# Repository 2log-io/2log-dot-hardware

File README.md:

# 2log-dot-hardware

This repository contains the KiCad Project for the 2log Dot. The hardware is designed to be used with [2log Dot](https://github.com/2log-io/2log-dot "2log Dot Firmware")

## Parts

The PCB consists of a 4-Layer stack. All required parts are through hole components with the exception of the capacitor C1 which is a combined footprint.
Besides the PCB itself you need the following parts:
  * 24 Led WS2812B Ring with 4 contacts (diameter 66mm)
  * SMD Capacitor 5mm diameter, about 10uF
  * (alternative) THT Capacitor, about 10uF
  * Wemos D1 mini ESP32 (ESP8266 will not work)
  * PN532 RFID Reader V3 (red modules, sold under elechouse brand or clones)
  * mini pushbutton (the tiny black/silver ones)
  * _(optional) 14 Pin Male and 13 Pin Female 2.54mm Pin Header/Socket for expansion port_
  
## Images

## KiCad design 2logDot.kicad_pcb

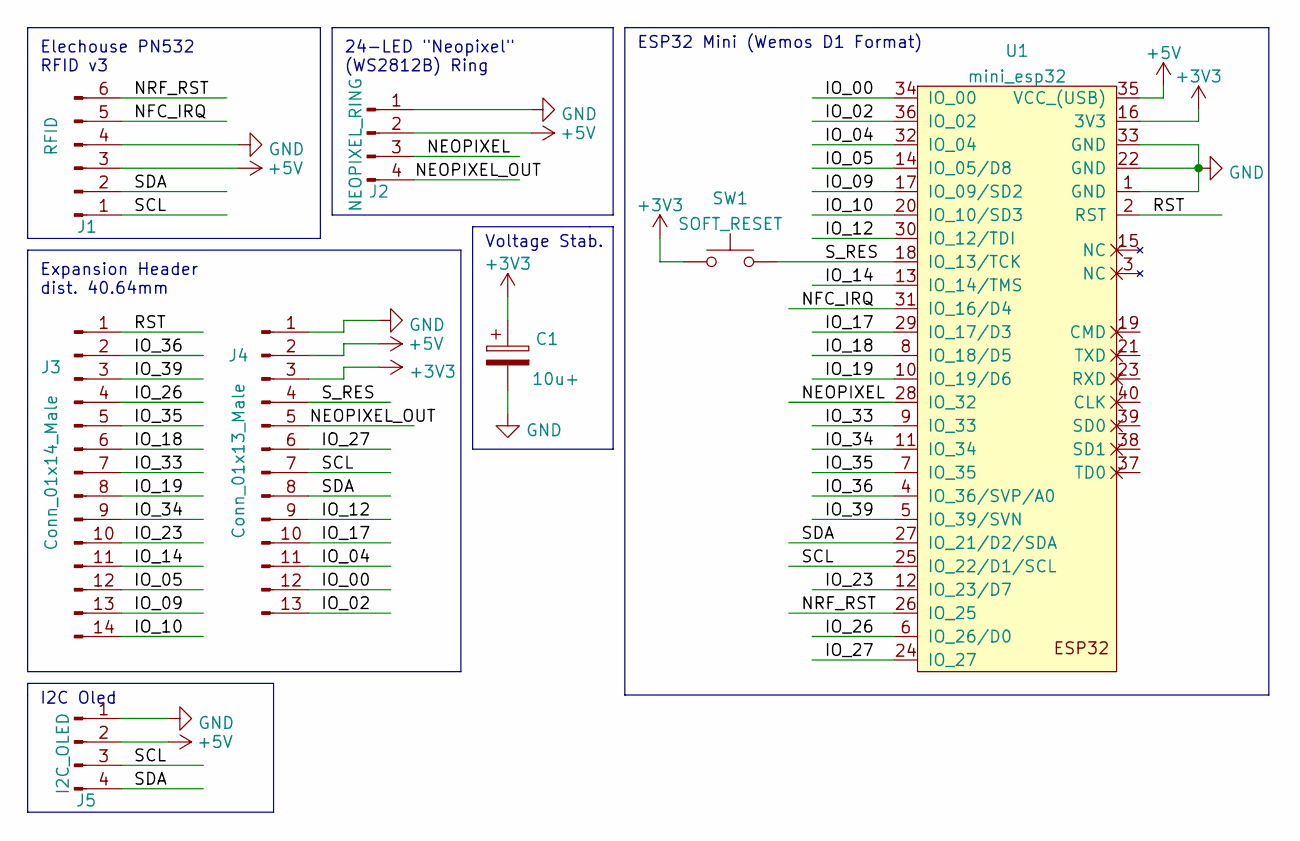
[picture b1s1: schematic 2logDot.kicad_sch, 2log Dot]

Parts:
C1: 10u+; CP_Elec_5x3
J1: RFID; 2log_elechouse_pn532
J2: NEOPIXEL_RING; PinHeader_1x04_P2.54mm_Vertical
J3: Conn_01x14_Male; PinHeader_1x14_P2.54mm_Vertical
J4: Conn_01x13_Male; PinSocket_1x13_P2.54mm_Vertical
J5: I2C_OLED; PinHeader_1x04_P2.54mm_Vertical
SW1: SOFT_RESET; SW_PUSH_6mm
U1: mini_esp32; ESP32_mini

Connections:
+3V3: C1.1, J4.3, SW1.1, U1.16 (3V3); also elsewhere on the board
+5V: J1.3, J2.2, J4.2, J5.2, U1.35 (VCC_(USB))
/IO_00: J4.12, U1.34 (IO_00)
/IO_02: J4.13, U1.36 (IO_02)
/IO_04: J4.11, U1.32 (IO_04)
/IO_05: J3.12, U1.14 (IO_05/D8)
/IO_09: J3.13, U1.17 (IO_09/SD2)
/IO_10: J3.14, U1.20 (IO_10/SD3)
/IO_12: J4.9, U1.30 (IO_12/TDI)
/IO_14: J3.11, U1.13 (IO_14/TMS)
/IO_17: J4.10, U1.29 (IO_17/D3)
/IO_18: J3.6, U1.8 (IO_18/D5)
/IO_19: J3.8, U1.10 (IO_19/D6)
/IO_23: J3.10, U1.12 (IO_23/D7)
/IO_26: J3.4, U1.6 (IO_26/D0)
/IO_27: J4.6, U1.24 (IO_27)
/IO_33: J3.7, U1.9 (IO_33)
/IO_34: J3.9, U1.11 (IO_34)
/IO_35: J3.5, U1.7 (IO_35)
/IO_36: J3.2, U1.4 (IO_36/SVP/A0)
/IO_39: J3.3, U1.5 (IO_39/SVN)
/NEOPIXEL: J2.3, U1.28 (IO_32)
/NEOPIXEL_OUT: J2.4, J4.5
/NFC_IRQ: J1.5, U1.31 (IO_16/D4)
/NRF_RST: J1.6, U1.26 (IO_25)
/RST: J3.1, U1.2 (RST)
/SCL: J1.1, J4.7, J5.3, U1.25 (IO_22/D1/SCL)
/SDA: J1.2, J4.8, J5.4, U1.27 (IO_21/D2/SDA)
/S_RES: J4.4, SW1.2, U1.18 (IO_13/TCK)
GND: C1.2, J1.4, J2.1, J4.1, J5.1, U1.1 (GND), U1.22 (GND), U1.33 (GND); also elsewhere on the board

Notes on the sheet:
I2C Oled
ESP32 Mini (Wemos D1 Format)
24-LED "Neopixel" (WS2812B) Ring
Voltage Stab.
Elechouse PN532 RFID v3
Expansion Header dist. 40.64mm

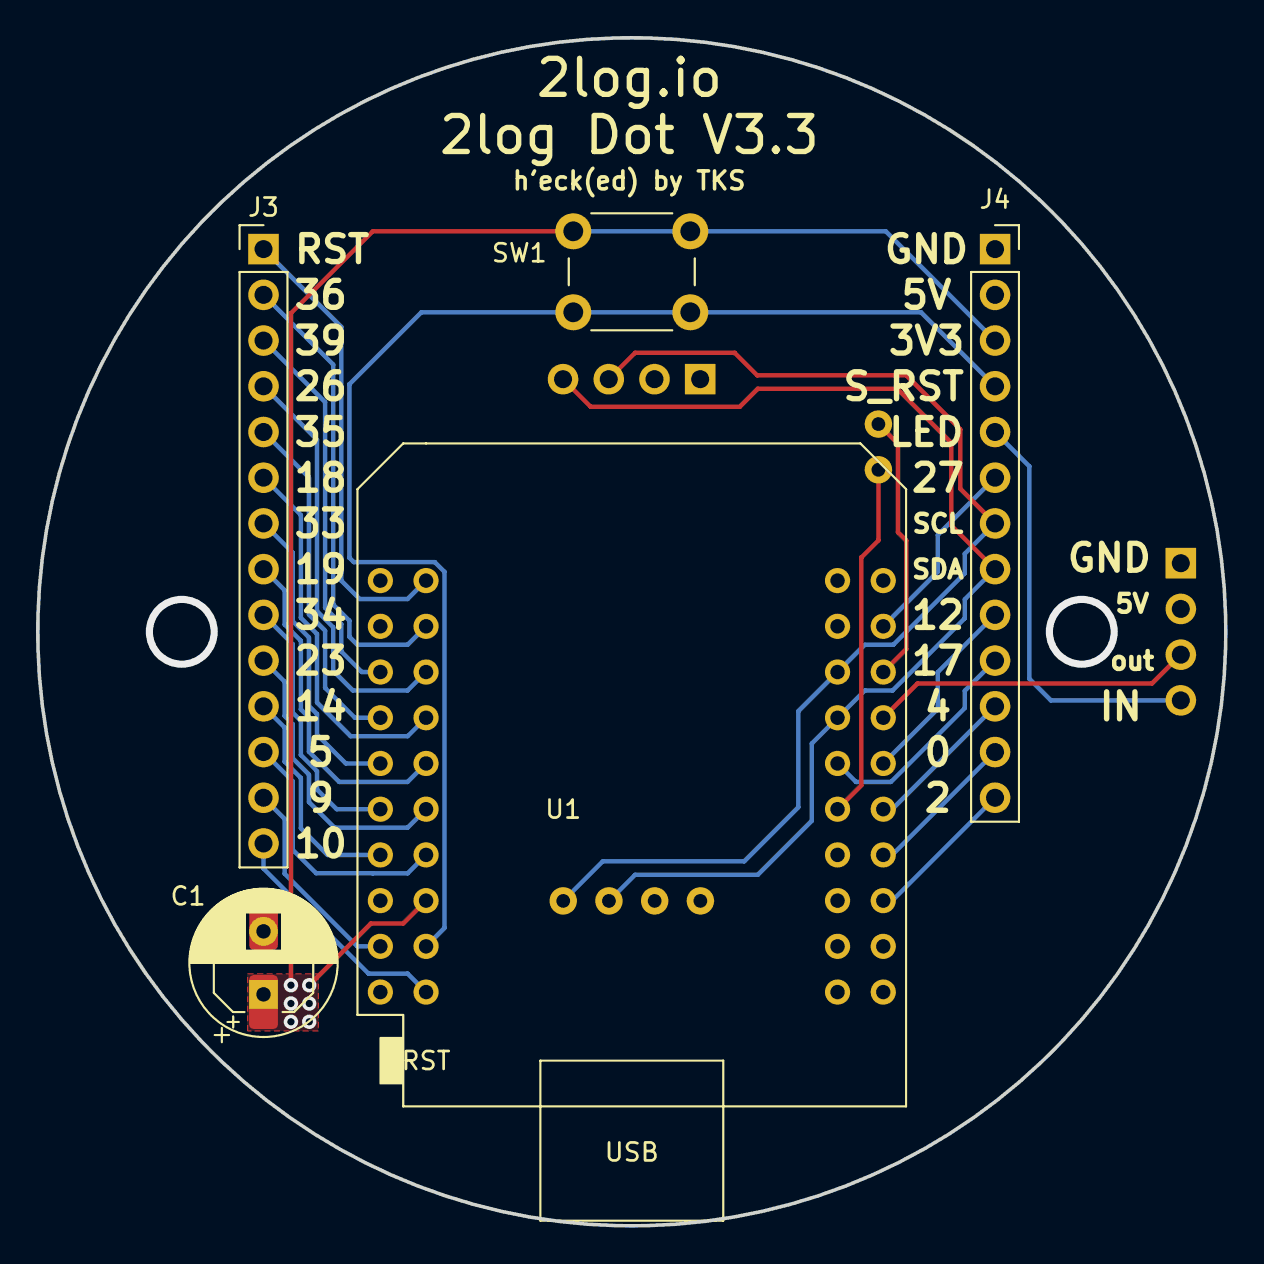
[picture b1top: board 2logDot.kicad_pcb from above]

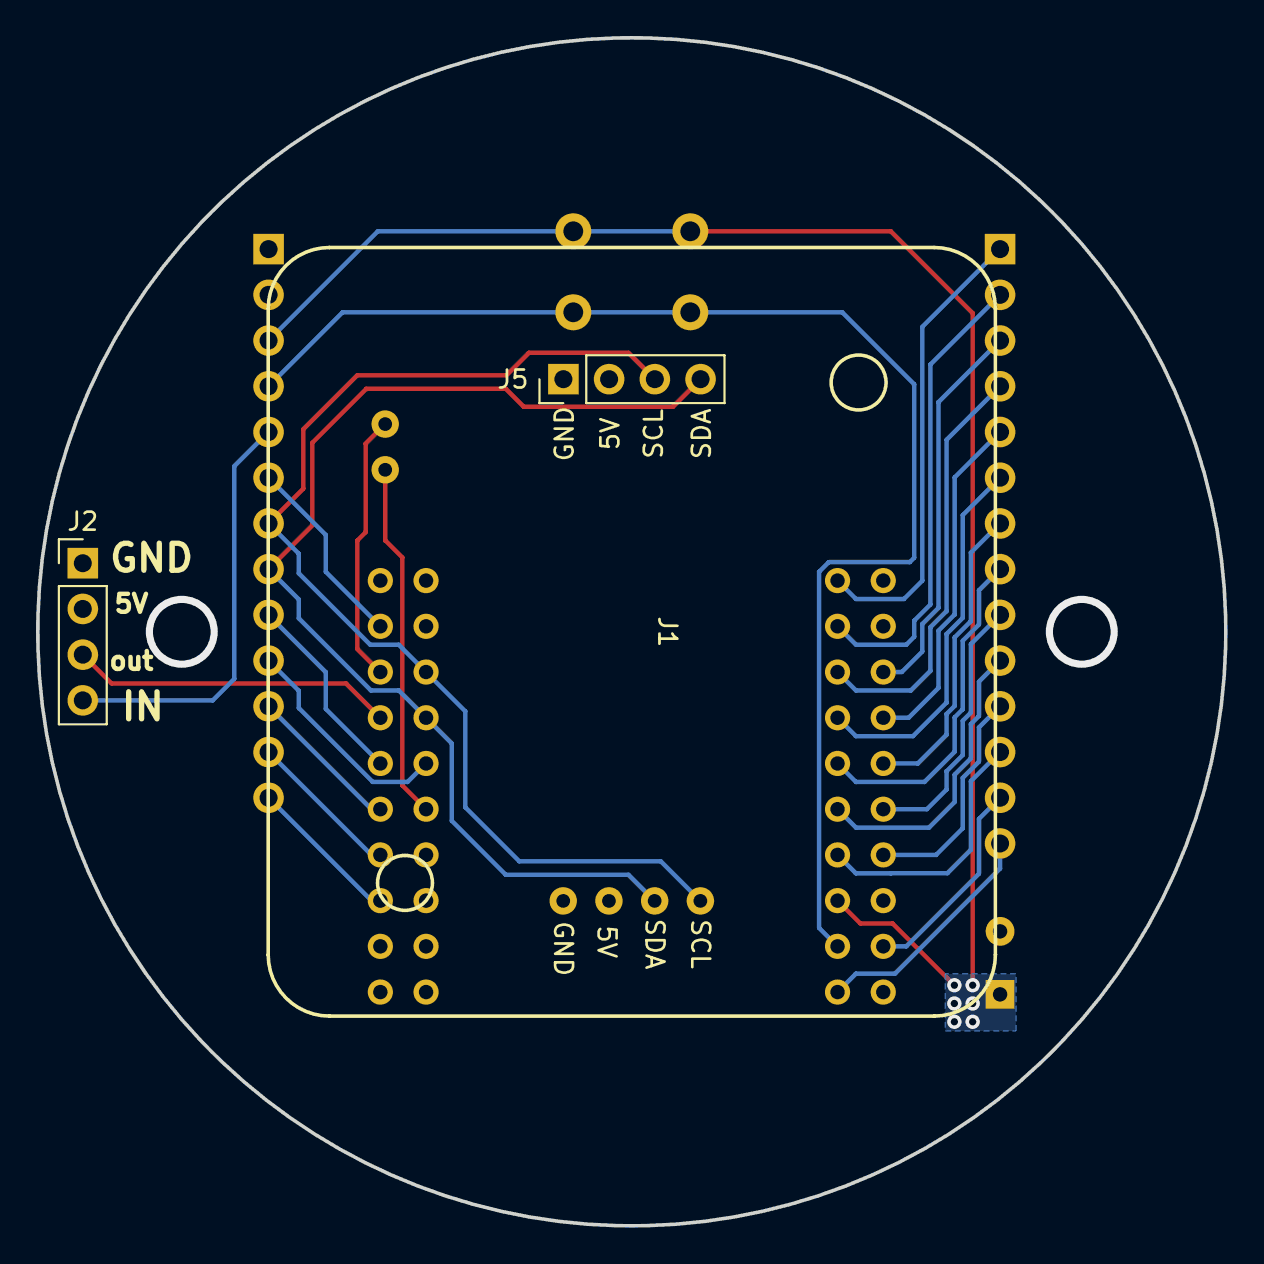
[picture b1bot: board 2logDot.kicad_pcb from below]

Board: 4 copper layers, 66.0 x 66.0 mm, 9 parts (3 on the bottom side), 30 nets.

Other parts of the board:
C1_ALT: CP_Radial_D8.0mm_P3.50mm

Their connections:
+3V3: C1_ALT.1; also elsewhere on the board
GND: C1_ALT.2; also elsewhere on the board

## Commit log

2022-02-10 Added V3.2
2022-02-26 Add .stl files
2022-07-01 added oled header
2022-11-02 flipped display to be able to center the screen
2022-11-02 added output to gitignore
